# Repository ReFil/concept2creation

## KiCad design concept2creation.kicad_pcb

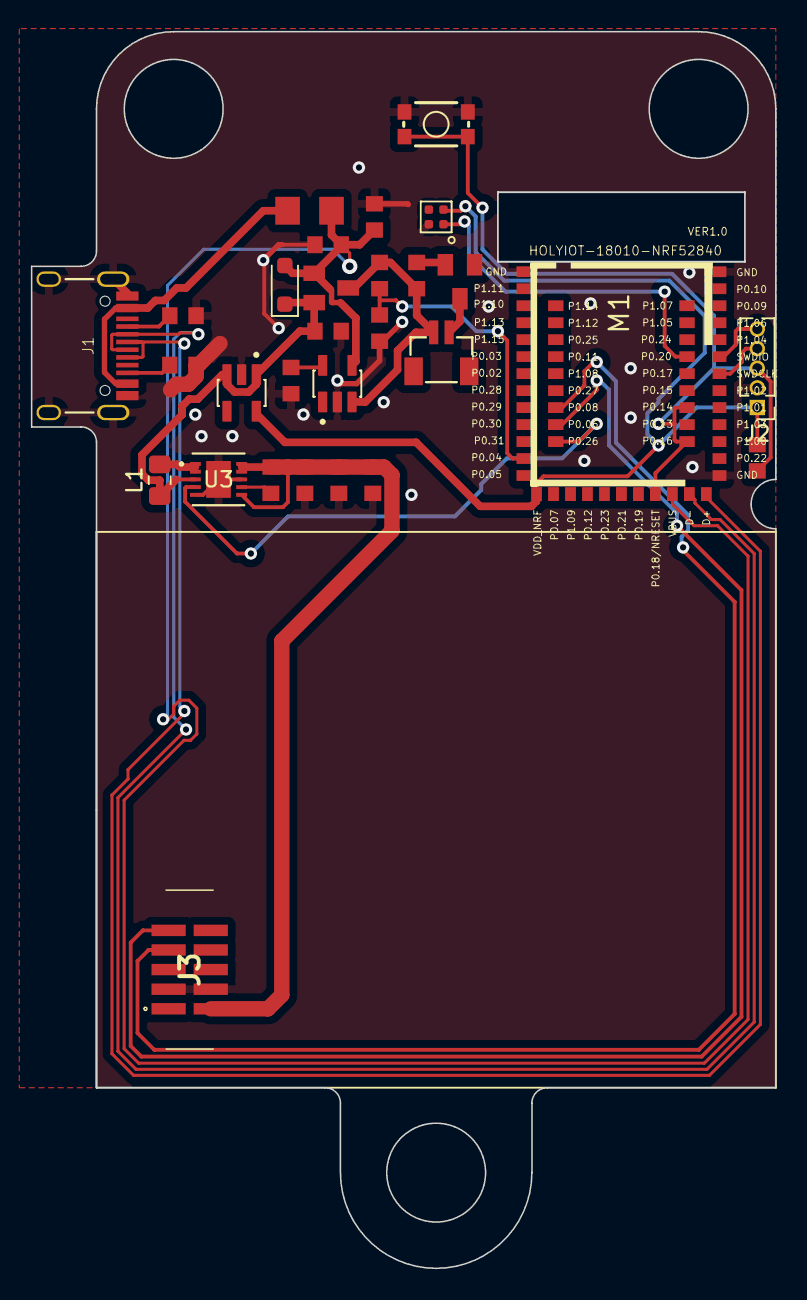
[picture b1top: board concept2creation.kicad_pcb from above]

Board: 2 copper layers, 48.2 x 80.1 mm, 29 parts (0 on the bottom side), 24 nets.

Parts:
C1, C3, C4: 10u; C0603
C2: 4.7u; C0603
C5: 2.2u; C0603
D122: SD103AWS-E3-08; D_SOD-323_HandSoldering
FUSE1: 500mA; 1206
J1: XKB-USB-C16PIN; XKB-USB-C-16P
J2: CONN_061.27MM; PinHeader_1x05_P1.27mm_Vertical
J3: Conn_01x10; HPMA115C0
L1: L; L_0805_2012Metric_Pad1.15x1.40mm_HandSolder
LED1: SK6805-E-J
M1: HOLYIOT_18010; HOLYIOT-18010
Q6: PMOSFETSOT23; SOT23
R1, R98: 100; 0603
R90, R91, R92, R96: 100k; 0603
R95: 2k; 0603
R99, R100: 5.1k; 0603
S1: MOMENTARY-SWITCH-SPST-SMD-4.6X2.8MM; TACTILE_SWITCH_SMD_4.6X2.8MM
U1: TP4054-42-SOT25-R_TP4054-42-SOT25-R; SOT95P285X140-5N
U2: XB3303ASOT23; SOT23
U3: max8815aetb+; 21-0137_T1033&plus_2_MXM
VREG1: AP2112K-3.3TRG1; SOT95P285X140-5N
X1: BM02B-SRSS-TB

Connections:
+3.3V: J2.1, LED1.2 (VDD), M1.VDD_NRF, R91.2, VREG1.5 (VOUT)
+5V: C3.1, C4.1, C5.1, J3.2, R1.2, U3.6 (FB), U3.9 (POUT), U3.10 (POUT)
+BATT: Q6.3 (D), R92.2, R98.1, U1.3 (BAT), X1.2
/5VEN: M1.P0.26, U3.4 (ON)
/NRF/BVOLT: M1.P0.04, R90.2, R92.1
/NRF/RST: J2.3, M1.P0.14, M1.P0.16, M1.P0.18, R91.1, S1.3 (2), S1.4 (2)
/NRF/SCK: J2.4, M1.SWDCLK
/NRF/SWD: J2.5, M1.SWDIO
/RX: J3.9, M1.P0.06
/TX: J3.7, M1.P0.08
/WS2812: LED1.1 (DIN), M1.P0.20
D+: J1.A6 (D+), J1.B6 (D+), M1.D+
D-: J1.A7 (D-), J1.B7 (D-), M1.D-
GND: C1.2, C2.2, C3.2, C4.2, C5.2, J1.GND, J1.GND2 (GND), J1.SHLD1 (SHLD), J2.2, J3.3, J3.4, LED1.4 (VSS), M1.GND (GND1), M1.GND1 (GND2), M1.GND2 (GND3), R90.1, R95.1, R96.1, R99.2, R100.2, S1.1, S1.2 (1), U1.2 (GND), U2.1 (VM), U3.5 (GND), U3.8 (SKIPB), U3.11 (EPAD), VREG1.2 (GND)
unnamed: FUSE1.1, J1.VBUS1 (VBUS), J1.VBUS2 (VBUS)
unnamed: J1.A5 (CC1), R99.1
unnamed: J1.B5 (CC2), R100.1
unnamed: L1.2, U3.1 (LX), U3.2 (LX)
unnamed: R95.2, U1.5 (PROG)
unnamed: U2.3 (GND), X1.1
unnamed: R98.2, U2.2 (VDD)
unnamed: R1.1, U3.7 (OUTS)
VBUS: C1.1, D122.2 (A), FUSE1.2, M1.VBUS, Q6.1 (G), R96.2, U1.4 (VCC)
V_RAW: C2.1, D122.1 (K), L1.1, Q6.2 (S), U3.3 (BATT), VREG1.1 (VIN), VREG1.3 (EN)

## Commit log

2023-07-14 Commit step file
2023-07-25 jhgbvkjh
2024-03-26 concept2creation
